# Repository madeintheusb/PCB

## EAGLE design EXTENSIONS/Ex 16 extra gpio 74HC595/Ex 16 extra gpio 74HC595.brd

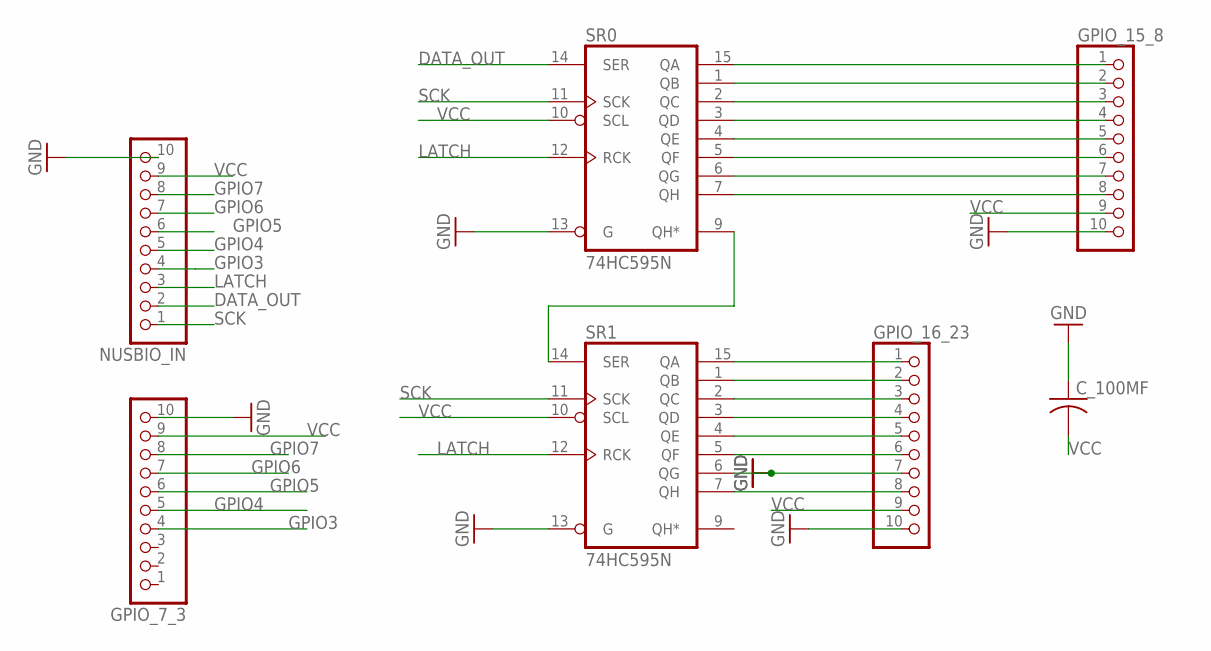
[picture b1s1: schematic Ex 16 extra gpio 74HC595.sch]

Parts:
C_100MF: C-US025-030X050; C025-030X050
GPIO_7_3, GPIO_15_8, GPIO_16_23: PINHD-1X10; 1X10-BIG
NUSBIO_IN: PINHD-1X10; 1X10-BIG
SR0, SR1: 74HC595N; DIL16

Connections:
DATA_OUT: NUSBIO_IN.2, SR0.14 (SER)
GND: C_100MF.1, GPIO_7_3.10, GPIO_15_8.10, GPIO_16_23.10, NUSBIO_IN.10, SR0.8 (GND), SR0.13 (G), SR1.8 (GND), SR1.13 (G)
GPIO3: GPIO_7_3.4, NUSBIO_IN.4
GPIO4: GPIO_7_3.5, NUSBIO_IN.5
GPIO5: GPIO_7_3.6, NUSBIO_IN.6
GPIO6: GPIO_7_3.7, NUSBIO_IN.7
GPIO7: GPIO_7_3.8, NUSBIO_IN.8
LATCH: NUSBIO_IN.3, SR0.12 (RCK), SR1.12 (RCK)
unnamed: GPIO_15_8.1, SR0.15 (QA)
unnamed: GPIO_15_8.2, SR0.1 (QB)
unnamed: GPIO_15_8.3, SR0.2 (QC)
unnamed: GPIO_15_8.4, SR0.3 (QD)
unnamed: GPIO_15_8.5, SR0.4 (QE)
unnamed: GPIO_15_8.6, SR0.5 (QF)
unnamed: GPIO_15_8.7, SR0.6 (QG)
unnamed: GPIO_15_8.8, SR0.7 (QH)
unnamed: SR0.9 (QH*), SR1.14 (SER)
unnamed: GPIO_16_23.1, SR1.15 (QA)
unnamed: GPIO_16_23.2, SR1.1 (QB)
unnamed: GPIO_16_23.3, SR1.2 (QC)
unnamed: GPIO_16_23.4, SR1.3 (QD)
unnamed: GPIO_16_23.5, SR1.4 (QE)
unnamed: GPIO_16_23.6, SR1.5 (QF)
unnamed: GPIO_16_23.7, SR1.6 (QG)
unnamed: GPIO_16_23.8, SR1.7 (QH)
SCK: NUSBIO_IN.1, SR0.11 (SCK), SR1.11 (SCK)
VCC: C_100MF.2, GPIO_7_3.9, GPIO_15_8.9, GPIO_16_23.9, NUSBIO_IN.9, SR0.10 (SCL), SR0.16 (VCC), SR1.10 (SCL), SR1.16 (VCC)

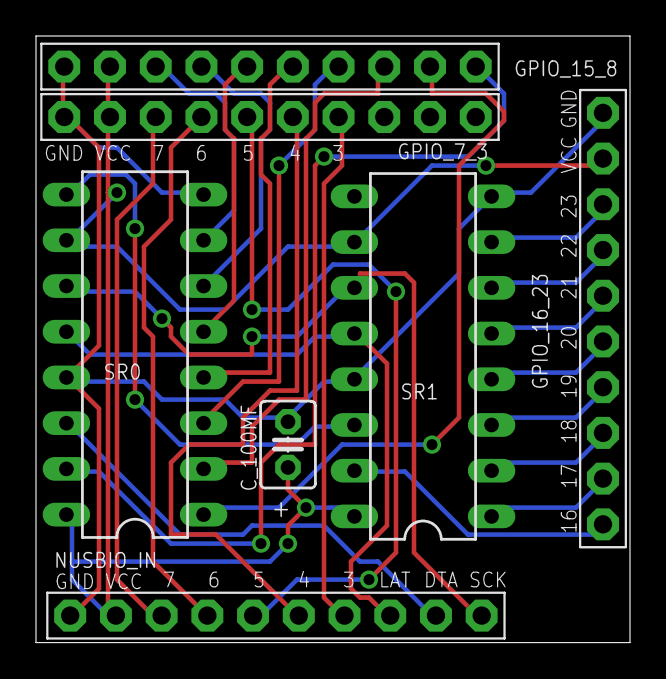
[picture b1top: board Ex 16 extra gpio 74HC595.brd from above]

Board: 2 copper layers, 33.0 x 33.7 mm, 7 parts (0 on the bottom side), 27 nets.

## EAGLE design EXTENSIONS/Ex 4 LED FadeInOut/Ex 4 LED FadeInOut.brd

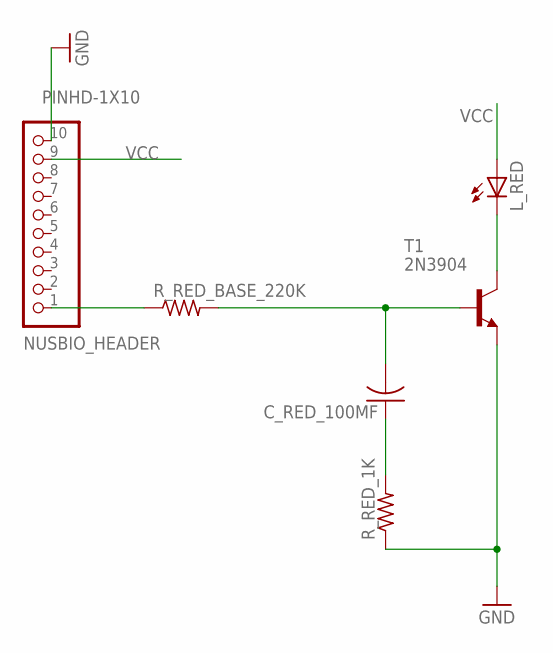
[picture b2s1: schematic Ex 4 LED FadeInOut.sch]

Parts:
C_RED_100MF: C-US025-030X050; C025-030X050
L_RED: LED5MM
NUSBIO_HEADER: PINHD-1X10; 1X10-BIG
R_RED_1K: R-US_0207/10; 0207/10
R_RED_BASE_220K: R-US_0207/10; 0207/10
T1: 2N3904; TO92

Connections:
GND: NUSBIO_HEADER.10, R_RED_1K.1, T1.3 (E)
unnamed: NUSBIO_HEADER.1, R_RED_BASE_220K.1
unnamed: C_RED_100MF.2, R_RED_BASE_220K.2, T1.2 (B)
unnamed: L_RED.K (C), T1.1 (C)
unnamed: C_RED_100MF.1, R_RED_1K.2
VCC: L_RED.A, NUSBIO_HEADER.9

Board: 2 copper layers, 6 parts (0 on the bottom side), 6 nets, no tracks yet.

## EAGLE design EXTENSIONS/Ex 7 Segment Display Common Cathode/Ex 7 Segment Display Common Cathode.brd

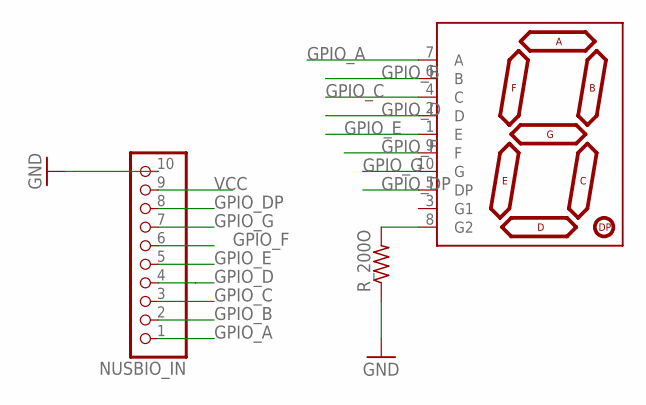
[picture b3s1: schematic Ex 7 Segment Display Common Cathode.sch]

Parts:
NUSBIO_IN: PINHD-1X10; 1X10-BIG
R_200O: R-US_R1206; R1206
U$1: 7-SEGMENT-DISPLAYPTH; 7-SEGMENT-DISPLAY

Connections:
GND: NUSBIO_IN.10, R_200O.1
GPIO_A: NUSBIO_IN.1, U$1.7 (A)
GPIO_B: NUSBIO_IN.2, U$1.6 (B)
GPIO_C: NUSBIO_IN.3, U$1.4 (C)
GPIO_D: NUSBIO_IN.4, U$1.2 (D)
GPIO_DP: NUSBIO_IN.8, U$1.5 (DP)
GPIO_E: NUSBIO_IN.5, U$1.1 (E)
GPIO_F: NUSBIO_IN.6, U$1.9 (F)
GPIO_G: NUSBIO_IN.7, U$1.10 (G)
unnamed: R_200O.2, U$1.8 (G2)
VCC: NUSBIO_IN.9

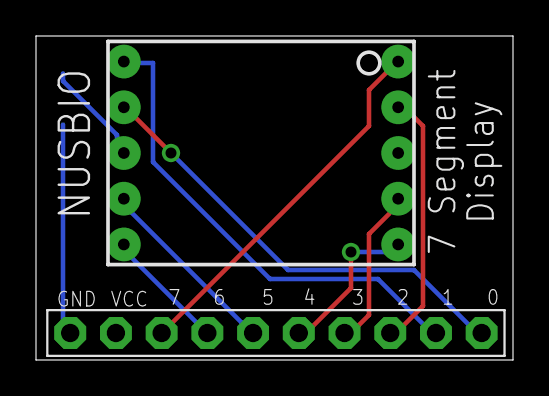
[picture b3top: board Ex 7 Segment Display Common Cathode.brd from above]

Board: 2 copper layers, 26.5 x 18.0 mm, 3 parts (1 on the bottom side), 10 nets.

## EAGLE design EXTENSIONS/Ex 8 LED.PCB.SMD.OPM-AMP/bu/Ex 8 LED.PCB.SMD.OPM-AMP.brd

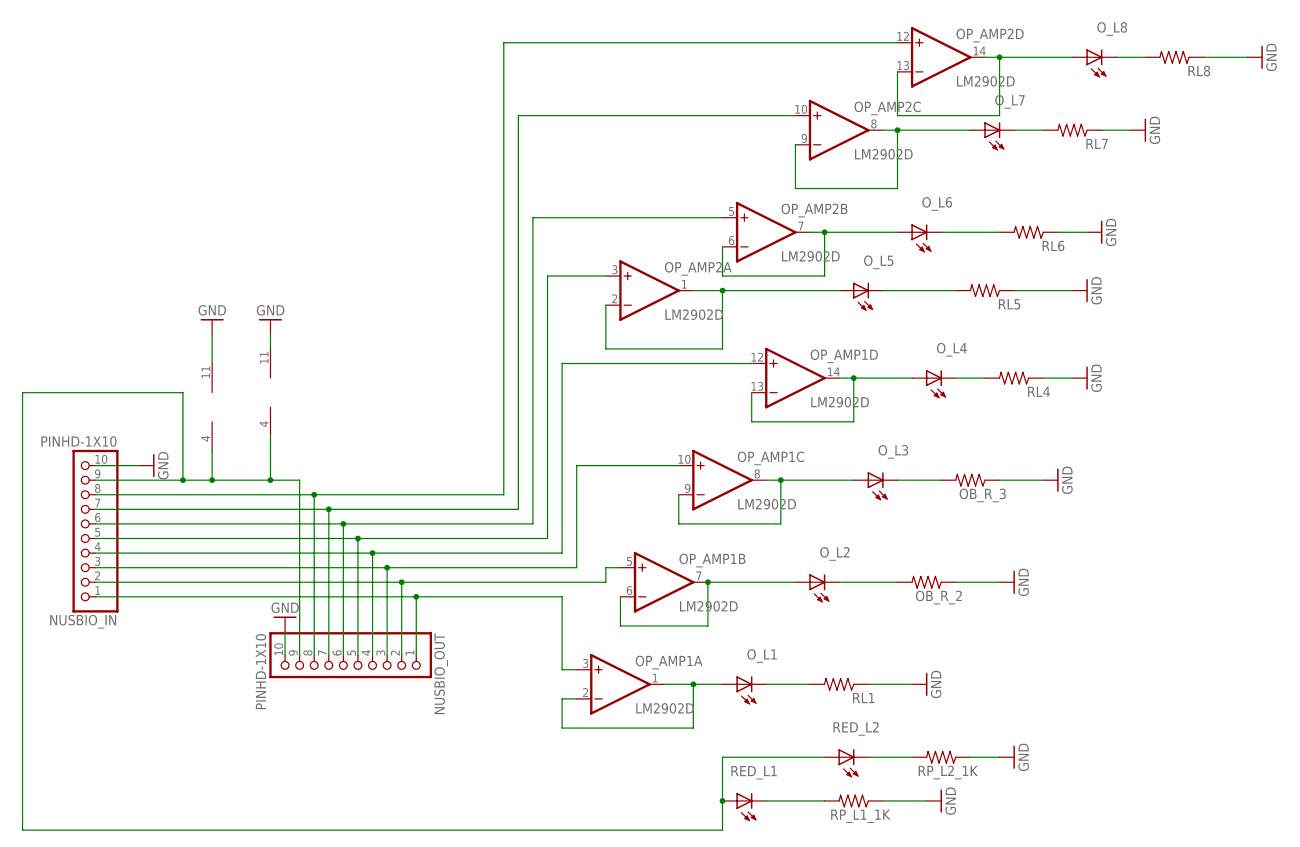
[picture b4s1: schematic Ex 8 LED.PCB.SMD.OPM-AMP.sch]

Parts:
NUSBIO_IN: PINHD-1X10; 1X10-BIG
NUSBIO_OUT: PINHD-1X10; 1X10-BIG
OB_R_2, OB_R_3: R-US_R0805; R0805
OP_AMP1, OP_AMP2: LM2902D; SO14
O_L1, O_L2, O_L3, O_L4, O_L5, O_L6, O_L7, O_L8: LEDCHIPLED_0805; CHIPLED_0805
RED_L1, RED_L2: LEDCHIPLED_0805; CHIPLED_0805
RL1, RL4, RL5, RL6, RL7, RL8: R-US_R0805; R0805
RP_L1_1K, RP_L2_1K: R-US_R0805; R0805

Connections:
GND: NUSBIO_IN.10, NUSBIO_OUT.10, OB_R_2.1, OB_R_3.1, OP_AMP1.11 (V-), OP_AMP2.11 (V-), RL1.1, RL4.1, RL5.1, RL6.1, RL7.1, RL8.1, RP_L1_1K.1, RP_L2_1K.1
unnamed: OP_AMP1.1 (OUT), OP_AMP1.2 (-IN), O_L1.A
unnamed: O_L1.C, RL1.2
unnamed: NUSBIO_IN.1, NUSBIO_OUT.1, OP_AMP1.3 (+IN)
unnamed: NUSBIO_IN.2, NUSBIO_OUT.2, OP_AMP1.5 (+IN)
unnamed: NUSBIO_IN.3, NUSBIO_OUT.3, OP_AMP1.10 (+IN)
unnamed: NUSBIO_IN.4, NUSBIO_OUT.4, OP_AMP1.12 (+IN)
unnamed: NUSBIO_IN.5, NUSBIO_OUT.5, OP_AMP2.3 (+IN)
unnamed: NUSBIO_IN.6, NUSBIO_OUT.6, OP_AMP2.5 (+IN)
unnamed: NUSBIO_IN.7, NUSBIO_OUT.7, OP_AMP2.10 (+IN)
unnamed: NUSBIO_IN.8, NUSBIO_OUT.8, OP_AMP2.12 (+IN)
unnamed: NUSBIO_IN.9, NUSBIO_OUT.9, OP_AMP1.4 (V+), OP_AMP2.4 (V+), RED_L1.A, RED_L2.A
unnamed: OP_AMP1.6 (-IN), OP_AMP1.7 (OUT), O_L2.A
unnamed: OP_AMP1.8 (OUT), OP_AMP1.9 (-IN), O_L3.A
unnamed: OB_R_3.2, O_L3.C
unnamed: OP_AMP1.13 (-IN), OP_AMP1.14 (OUT), O_L4.A
unnamed: OP_AMP2.1 (OUT), OP_AMP2.2 (-IN), O_L5.A
unnamed: O_L5.C, RL5.2
unnamed: OP_AMP2.6 (-IN), OP_AMP2.7 (OUT), O_L6.A
unnamed: O_L6.C, RL6.2
unnamed: OP_AMP2.8 (OUT), OP_AMP2.9 (-IN), O_L7.A
unnamed: O_L7.C, RL7.2
unnamed: OP_AMP2.13 (-IN), OP_AMP2.14 (OUT), O_L8.A
unnamed: O_L8.C, RL8.2
unnamed: RED_L1.C, RP_L1_1K.2
unnamed: RED_L2.C, RP_L2_1K.2
O_L2: OB_R_2.2, O_L2.C
O_L4: O_L4.C, RL4.2

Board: 2 copper layers, 24 parts (0 on the bottom side), 28 nets, no tracks yet.

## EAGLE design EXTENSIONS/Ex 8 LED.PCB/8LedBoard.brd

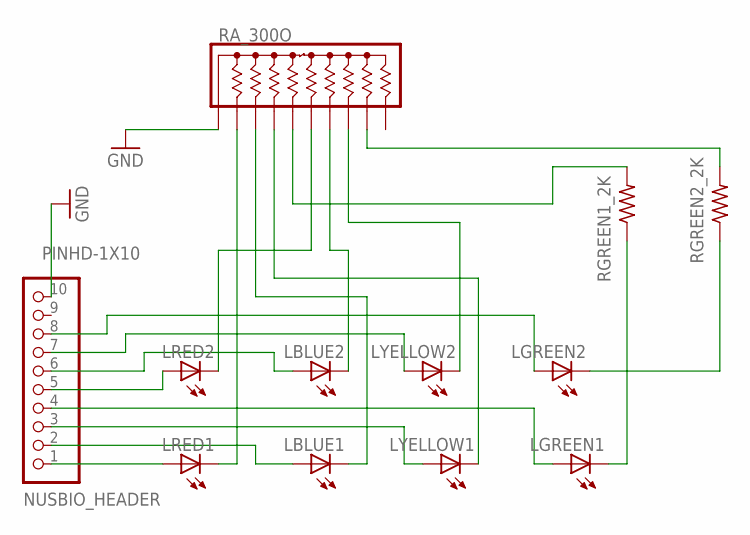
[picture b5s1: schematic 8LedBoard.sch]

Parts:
LBLUE1, LBLUE2: LED5MM
LGREEN1, LGREEN2: LED5MM
LRED1, LRED2: LED5MM
LYELLOW1, LYELLOW2: LED5MM
NUSBIO_HEADER: PINHD-1X10; 1X10-BIG
RA_300O: 4610X; SIP10
RGREEN1_2K, RGREEN2_2K: R-US_0207/10; 0207/10

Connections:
GND: NUSBIO_HEADER.10, RA_300O.1
unnamed: LGREEN2.A, NUSBIO_HEADER.8
unnamed: LRED1.A, NUSBIO_HEADER.1
unnamed: LBLUE1.A, NUSBIO_HEADER.2
unnamed: LYELLOW1.A, NUSBIO_HEADER.3
unnamed: LGREEN1.A, NUSBIO_HEADER.4
unnamed: LRED2.A, NUSBIO_HEADER.5
unnamed: LBLUE2.A, NUSBIO_HEADER.6
unnamed: LYELLOW2.A, NUSBIO_HEADER.7
unnamed: LRED1.K (C), RA_300O.2
unnamed: LBLUE1.K (C), RA_300O.3
unnamed: LYELLOW1.K (C), RA_300O.4
unnamed: LRED2.K (C), RA_300O.6
unnamed: LBLUE2.K (C), RA_300O.7
unnamed: LYELLOW2.K (C), RA_300O.8
unnamed: LGREEN1.K (C), RGREEN1_2K.1
unnamed: RA_300O.5, RGREEN1_2K.2
unnamed: LGREEN2.K (C), RGREEN2_2K.1
unnamed: RA_300O.9, RGREEN2_2K.2

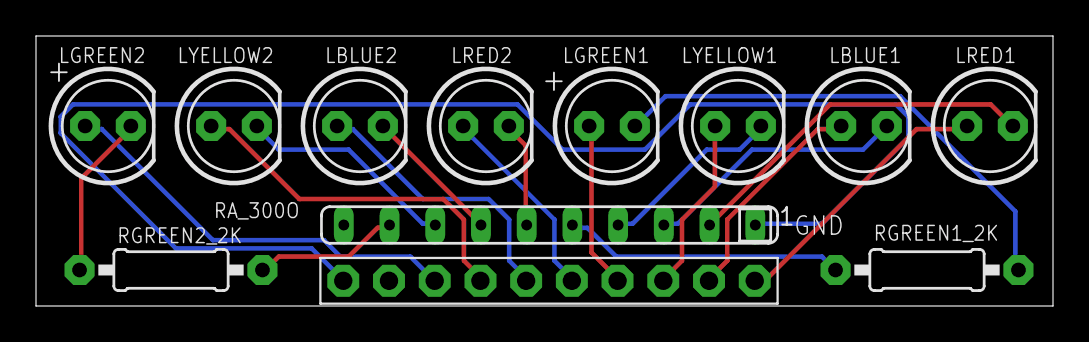
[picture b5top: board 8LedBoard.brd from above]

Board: 2 copper layers, 56.5 x 15.0 mm, 12 parts (0 on the bottom side), 19 nets.

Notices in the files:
parts and their libraries:
SparkFun-Displays: Licensing: Creative Commons ShareAlike 4.0 International - https://creativecommons.org/licenses/by-sa/4.0
